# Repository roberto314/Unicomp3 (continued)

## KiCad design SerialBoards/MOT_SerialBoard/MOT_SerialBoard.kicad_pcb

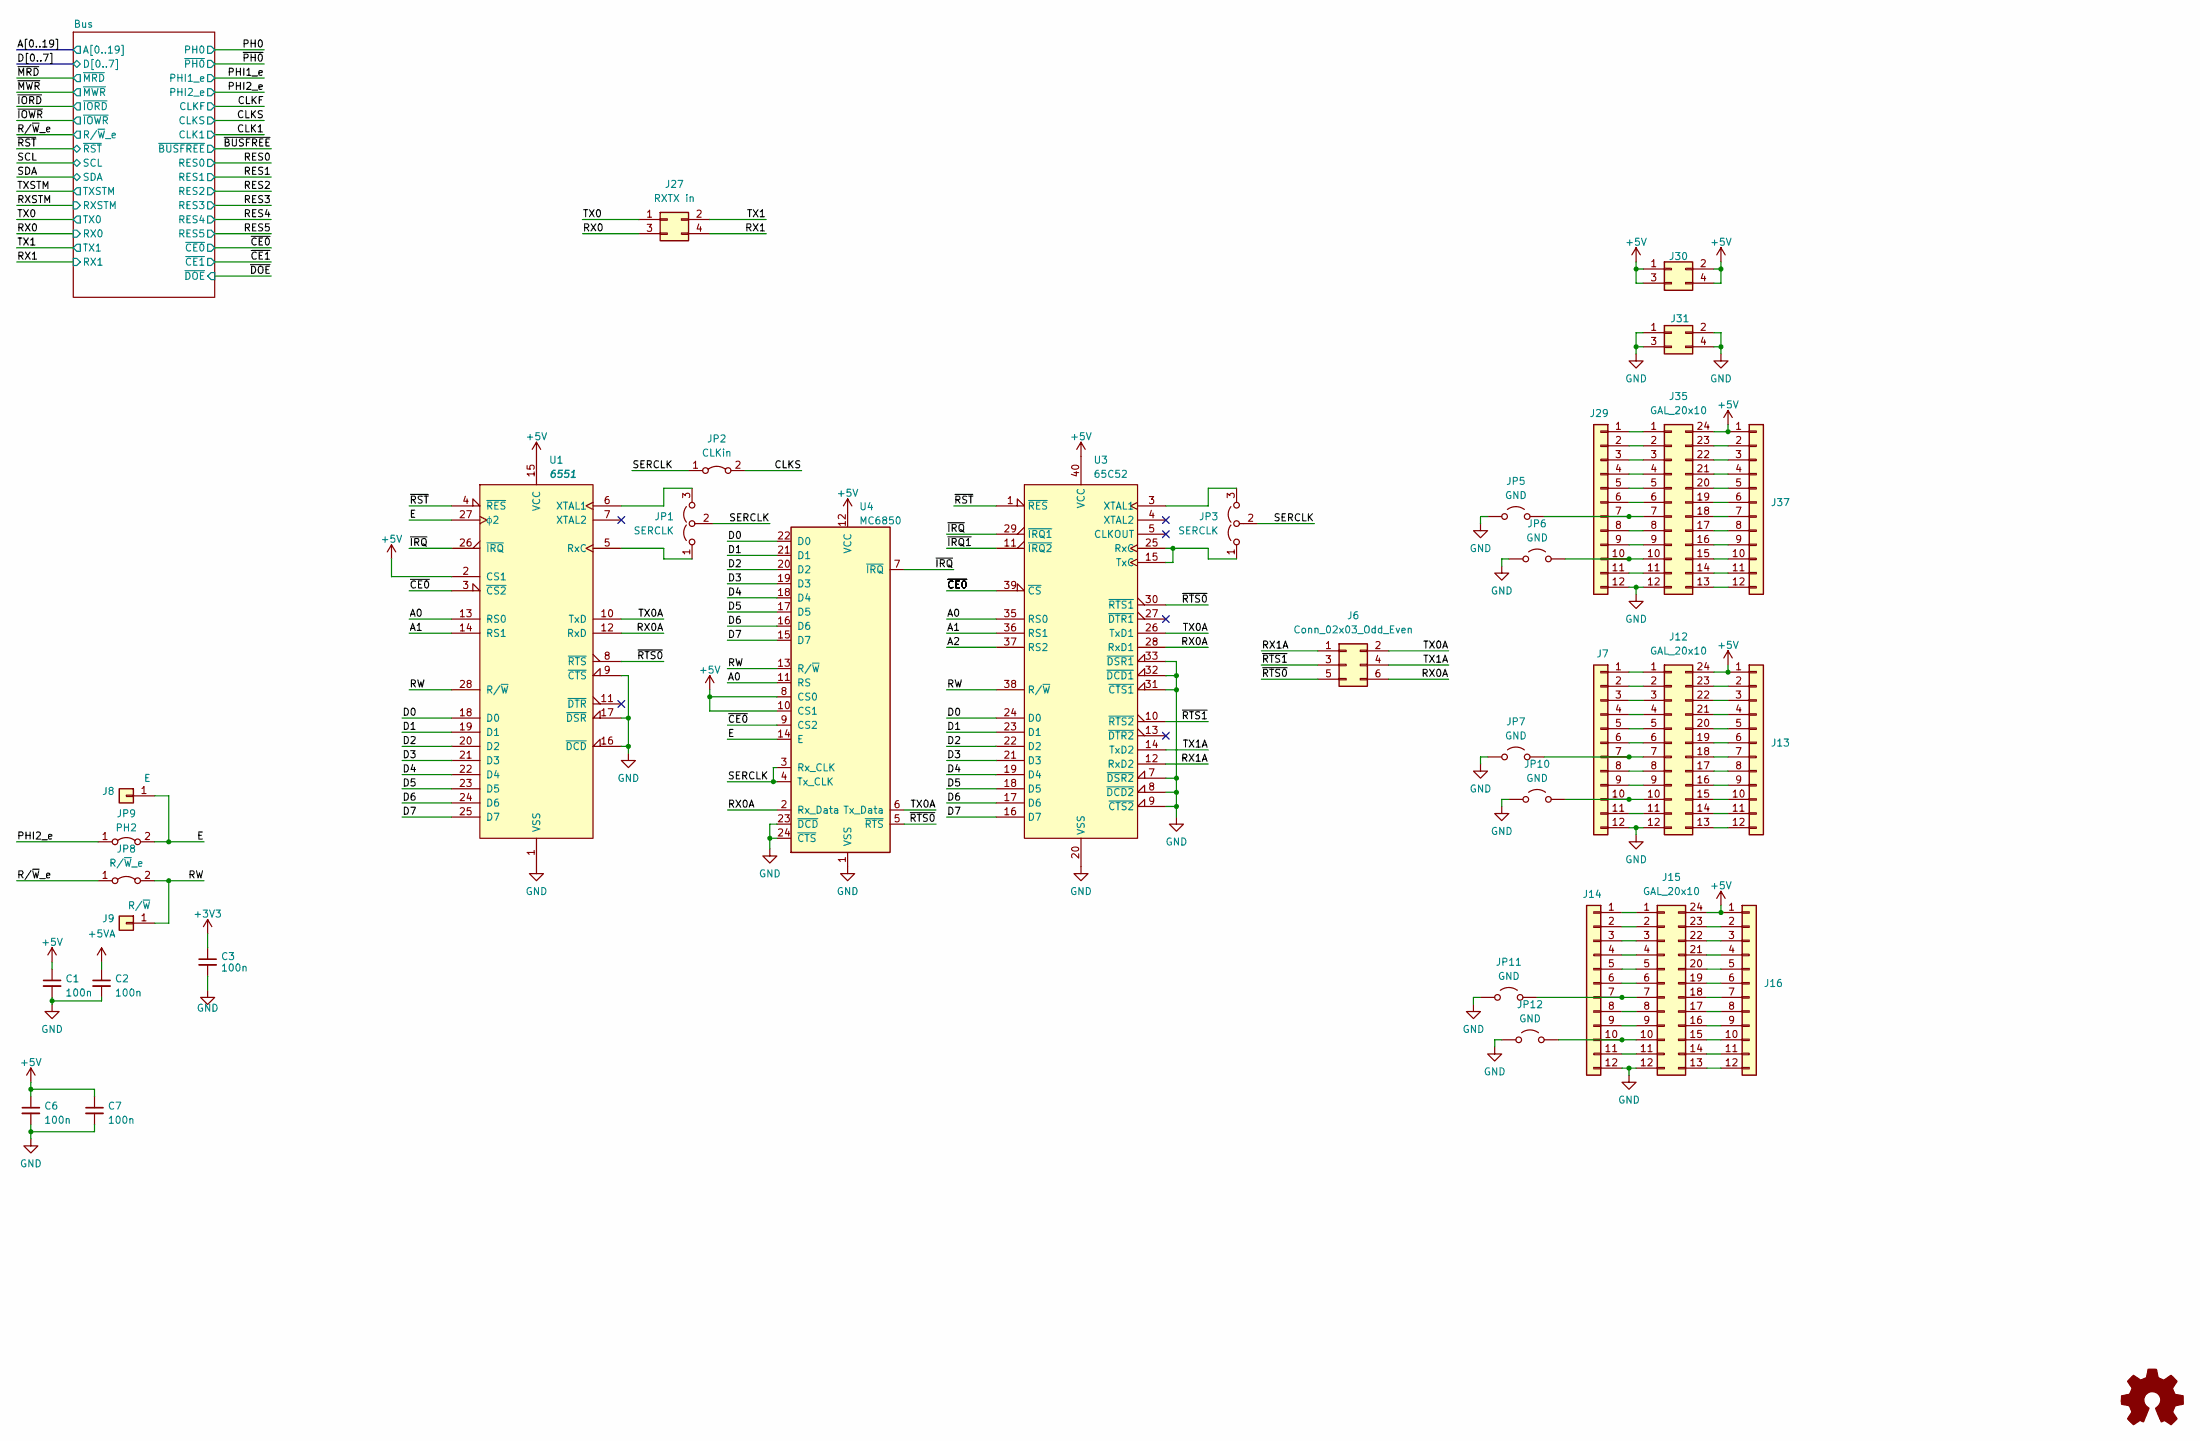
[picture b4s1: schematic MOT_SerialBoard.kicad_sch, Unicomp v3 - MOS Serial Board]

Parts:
C1, C2, C3, C6, C7: 100n; C_1206_3216Metric
J6: Conn_02x03_Odd_Even; PinSocket_2x03_P2.54mm_Vertical
J7, J13, J14, J16, J29, J37: Conn_01x12; PinSocket_1x12_P2.54mm_Vertical
J8: E; PinHeader_1x01_P2.00mm_Vertical
J9: R/~{W}; PinHeader_1x01_P2.00mm_Vertical
J12, J15, J35: GAL_20x10; DIP-24_W7.62mm
J27: RXTX in; PinSocket_2x02_P2.54mm_Vertical
J30, J31: Conn_02x02_Odd_Even; PinSocket_2x02_P2.54mm_Vertical
JP1, JP3: SERCLK; PinHeader_1x03_P2.54mm_Vertical
JP2: CLKin; SolderJumper-2_P1.3mm_Bridged_RoundedPad1.0x1.5mm
JP5, JP6, JP7, JP10, JP11, JP12: GND; SolderJumper-2_P1.3mm_Open_RoundedPad1.0x1.5mm
JP8: R/~{W}_e; SolderJumper-2_P1.3mm_Bridged_RoundedPad1.0x1.5mm
JP9: PH2; SolderJumper-2_P1.3mm_Bridged_RoundedPad1.0x1.5mm
U1: 6551; DIP-28_W15.24mm_LongPads
U3: 65C52; DIP-40_W15.24mm_Socket_LongPads
U4: MC6850; DIP-24_W15.24mm_LongPads

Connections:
+3V3: C3.1; also elsewhere on the board
+5V: C1.1, C6.1, C7.1, J12.24, J13.1, J15.24, J16.1, J30.1, J30.2, J30.3, J30.4, J35.24, J37.1, U1.2 (CS1), U1.15 (VCC), U3.40 (VCC), U4.8 (CS0), U4.10 (CS1), U4.12 (VCC); also elsewhere on the board
+5VA: C2.1; also elsewhere on the board
/A0: U1.13 (RS0), U3.35 (RS0), U4.11 (RS); also elsewhere on the board
/A1: U1.14 (RS1), U3.36 (RS1); also elsewhere on the board
/A2: U3.37 (RS2); also elsewhere on the board
/CLKS: JP2.2 (B); also elsewhere on the board
/D0: U1.18 (D0), U3.24 (D0), U4.22 (D0); also elsewhere on the board
/D1: U1.19 (D1), U3.23 (D1), U4.21 (D1); also elsewhere on the board
/D2: U1.20 (D2), U3.22 (D2), U4.20 (D2); also elsewhere on the board
/D3: U1.21 (D3), U3.21 (D3), U4.19 (D3); also elsewhere on the board
/D4: U1.22 (D4), U3.19 (D4), U4.18 (D4); also elsewhere on the board
/D5: U1.23 (D5), U3.18 (D5), U4.17 (D5); also elsewhere on the board
/D6: U1.24 (D6), U3.17 (D6), U4.16 (D6); also elsewhere on the board
/D7: U1.25 (D7), U3.16 (D7), U4.15 (D7); also elsewhere on the board
/E: J8.1, JP9.2 (B), U1.27 (ϕ2), U4.14 (E)
/PHI2_e: JP9.1 (A); also elsewhere on the board
/RW: J9.1, JP8.2 (B), U1.28 (R/~W), U3.38 (R/~W), U4.13 (R/~W)
/RX0: J27.3; also elsewhere on the board
/RX0A: J6.6, U1.12 (RxD), U3.28 (RxD1), U4.2 (Rx_Data)
/RX1: J27.4; also elsewhere on the board
/RX1A: J6.1, U3.12 (RxD2)
/R/~W_e: JP8.1 (A); also elsewhere on the board
/SERCLK: JP1.2 (C), JP2.1 (A), JP3.2 (C), U4.3 (Rx_CLK), U4.4 (Tx_CLK)
/TX0: J27.1; also elsewhere on the board
/TX0A: J6.2, U1.10 (TxD), U3.26 (TxD1), U4.6 (Tx_Data)
/TX1: J27.2; also elsewhere on the board
/TX1A: J6.4, U3.14 (TxD2)
/~CE0: U1.3 (~CS2), U3.39 (~CS), U4.9 (CS2); also elsewhere on the board
/~IRQ1: U3.11 (~IRQ2)
/~IRQ: U1.26 (~IRQ), U3.29 (~IRQ1), U4.7 (~IRQ)
/~RST: U1.4 (~RES), U3.1 (~RES); also elsewhere on the board
/~RTS0: J6.5, U1.8 (~RTS), U3.30 (~RTS1), U4.5 (~RTS)
/~RTS1: J6.3, U3.10 (~RTS2)
GND: C1.2, C2.2, C3.2, C6.2, C7.2, J7.12, J12.12, J14.12, J15.12, J29.12, J31.1, J31.2, J31.3, J31.4, J35.12, JP5.1 (A), JP6.1 (A), JP7.1 (A), JP10.1 (A), JP11.1 (A), JP12.1 (A), U1.1 (VSS), U1.9 (~CTS), U1.16 (~DCD), U1.17 (~DSR), U3.7 (~DSR2), U3.8 (~DCD2), U3.9 (~CTS2), U3.20 (VSS), U3.31 (~CTS1), U3.32 (~DCD1), U3.33 (~DSR1), U4.1 (VSS), U4.23 (~DCD), U4.24 (~CTS); also elsewhere on the board
unnamed: J7.1, J12.1
unnamed: J7.2, J12.2
unnamed: J7.3, J12.3
unnamed: J7.4, J12.4
unnamed: J7.5, J12.5
unnamed: J7.6, J12.6
unnamed: J7.7, J12.7, JP7.2 (B)
unnamed: J7.8, J12.8
unnamed: J7.9, J12.9
unnamed: J7.10, J12.10, JP10.2 (B)
unnamed: J7.11, J12.11
unnamed: J12.13, J13.12
unnamed: J12.14, J13.11
unnamed: J12.15, J13.10
unnamed: J12.16, J13.9
unnamed: J12.17, J13.8
unnamed: J12.18, J13.7
unnamed: J12.19, J13.6
unnamed: J12.20, J13.5
unnamed: J12.21, J13.4
unnamed: J12.22, J13.3
unnamed: J12.23, J13.2
unnamed: J14.1, J15.1
unnamed: J14.2, J15.2
unnamed: J14.3, J15.3
unnamed: J14.4, J15.4
unnamed: J14.5, J15.5
unnamed: J14.6, J15.6
unnamed: J14.7, J15.7, JP11.2 (B)
unnamed: J14.8, J15.8
unnamed: J14.9, J15.9
unnamed: J14.10, J15.10, JP12.2 (B)
unnamed: J14.11, J15.11
unnamed: J15.13, J16.12
unnamed: J15.14, J16.11
unnamed: J15.15, J16.10
unnamed: J15.16, J16.9
unnamed: J15.17, J16.8
unnamed: J15.18, J16.7
unnamed: J15.19, J16.6
unnamed: J15.20, J16.5
unnamed: J15.21, J16.4
unnamed: J15.22, J16.3
unnamed: J15.23, J16.2
unnamed: J29.1, J35.1
unnamed: J29.2, J35.2
unnamed: J29.3, J35.3
unnamed: J29.4, J35.4
unnamed: J29.5, J35.5
unnamed: J29.6, J35.6
unnamed: J29.7, J35.7, JP5.2 (B)
unnamed: J29.8, J35.8
unnamed: J29.9, J35.9
unnamed: J29.10, J35.10, JP6.2 (B)
unnamed: J29.11, J35.11
unnamed: J35.13, J37.12
unnamed: J35.14, J37.11
unnamed: J35.15, J37.10
unnamed: J35.16, J37.9
unnamed: J35.17, J37.8
unnamed: J35.18, J37.7
unnamed: J35.19, J37.6
unnamed: J35.20, J37.5
unnamed: J35.21, J37.4
unnamed: J35.22, J37.3
unnamed: J35.23, J37.2
unnamed: JP1.1 (A), U1.5 (RxC)
unnamed: JP1.3 (B), U1.6 (XTAL1)
unnamed: JP3.1 (A), U3.15 (TxC), U3.25 (RxC)
unnamed: JP3.3 (B), U3.3 (XTAL1)

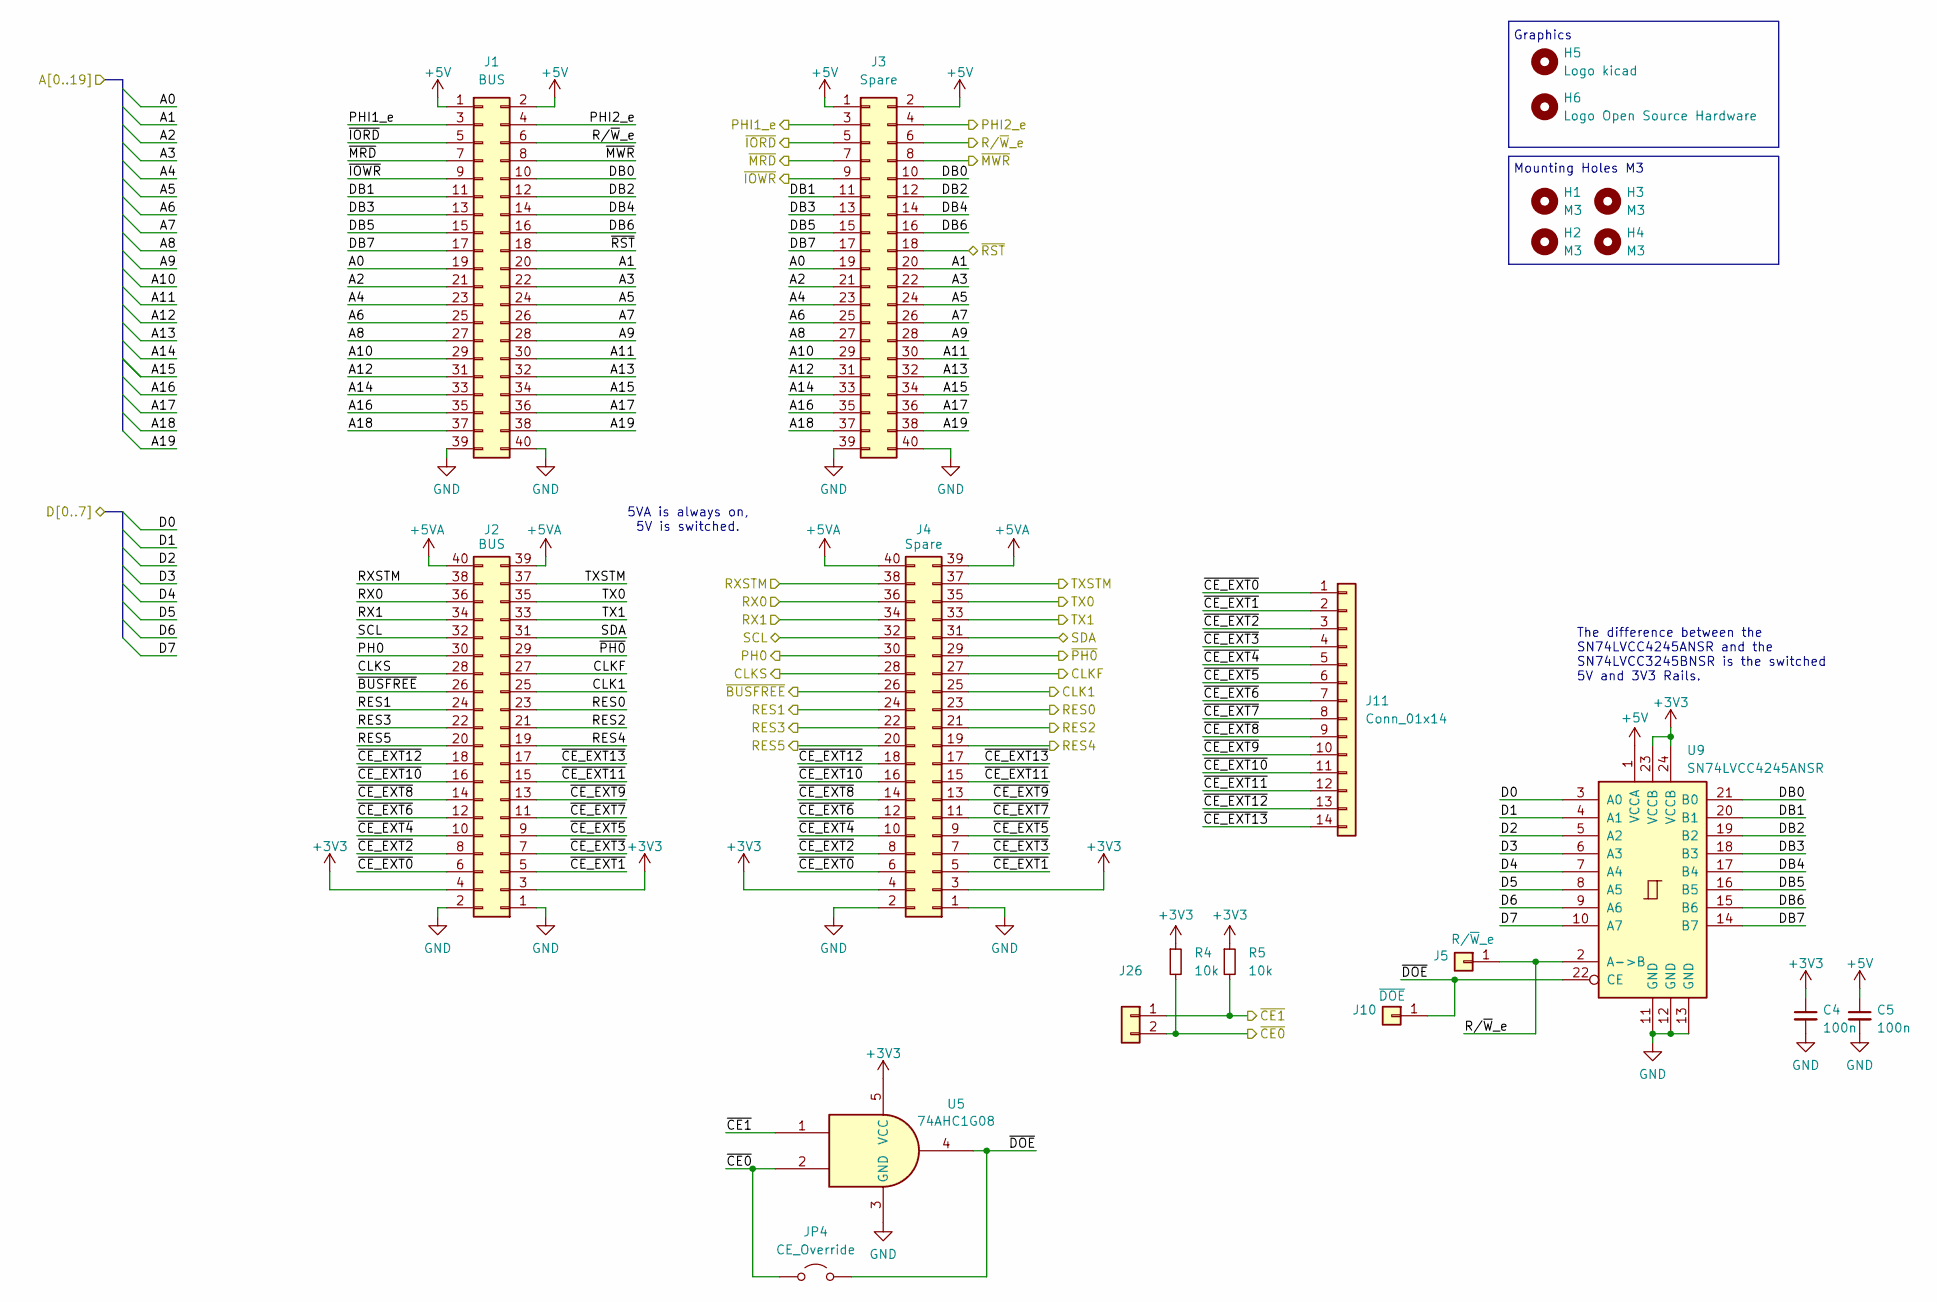
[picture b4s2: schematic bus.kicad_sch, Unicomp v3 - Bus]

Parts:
C4, C5: 100n; C_1206_3216Metric
H1, H2, H3, H4: M3; MountingHole_3.2mm_M3
H5: Logo kicad; KiCad-Logo2_6mm_SilkScreen
H6: Logo Open Source Hardware; OSHW-Logo2_7.3x6mm_SilkScreen
J1, J2: BUS; PinSocket_2x20_P2.54mm_Vertical
J3, J4: Spare; PinSocket_2x20_P2.54mm_Vertical
J5: R/~{W}_e; PinHeader_1x01_P2.00mm_Vertical
J10: ~{DOE}; PinHeader_1x01_P2.00mm_Vertical
J11: Conn_01x14; PinSocket_1x14_P2.54mm_Vertical
J26: Conn_01x02; PinSocket_1x02_P2.54mm_Vertical
JP4: CE_Override; SolderJumper-2_P1.3mm_Open_RoundedPad1.0x1.5mm
R4, R5: 10k; R_1206_3216Metric_Pad1.30x1.75mm_HandSolder
U5: 74AHC1G08; SOT-23-5_HandSoldering
U9: SN74LVCC4245ANSR; SO-24_5.3x15mm_P1.27mm

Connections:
+3V3: C4.1, J2.3, J2.4, J4.3, J4.4, R4.1, R5.1, U5.5 (VCC), U9.23 (VCCB), U9.24 (VCCB); also elsewhere on the board
+5V: C5.1, J1.1, J1.2, J3.1, J3.2, U9.1 (VCCA); also elsewhere on the board
+5VA: J2.39, J2.40, J4.39, J4.40; also elsewhere on the board
/A0: J1.19, J3.19; also elsewhere on the board
/A1: J1.20, J3.20; also elsewhere on the board
/A2: J1.21, J3.21; also elsewhere on the board
/A3: J1.22, J3.22
/A4: J1.23, J3.23
/A5: J1.24, J3.24
/A6: J1.25, J3.25
/A7: J1.26, J3.26
/A8: J1.27, J3.27
/A9: J1.28, J3.28
/A10: J1.29, J3.29
/A11: J1.30, J3.30
/A12: J1.31, J3.31
/A13: J1.32, J3.32
/A14: J1.33, J3.33
/A15: J1.34, J3.34
/A16: J1.35, J3.35
/A17: J1.36, J3.36
/A18: J1.37, J3.37
/A19: J1.38, J3.38
/Bus/DB0: J1.10, J3.10, U9.21 (B0)
/Bus/DB1: J1.11, J3.11, U9.20 (B1)
/Bus/DB2: J1.12, J3.12, U9.19 (B2)
/Bus/DB3: J1.13, J3.13, U9.18 (B3)
/Bus/DB4: J1.14, J3.14, U9.17 (B4)
/Bus/DB5: J1.15, J3.15, U9.16 (B5)
/Bus/DB6: J1.16, J3.16, U9.15 (B6)
/Bus/DB7: J1.17, J3.17, U9.14 (B7)
/Bus/~CE_EXT0: J2.6, J4.6, J11.1
/Bus/~CE_EXT1: J2.5, J4.5, J11.2
/Bus/~CE_EXT2: J2.8, J4.8, J11.3
/Bus/~CE_EXT3: J2.7, J4.7, J11.4
/Bus/~CE_EXT4: J2.10, J4.10, J11.5
/Bus/~CE_EXT5: J2.9, J4.9, J11.6
/Bus/~CE_EXT6: J2.12, J4.12, J11.7
/Bus/~CE_EXT7: J2.11, J4.11, J11.8
/Bus/~CE_EXT8: J2.14, J4.14, J11.9
/Bus/~CE_EXT9: J2.13, J4.13, J11.10
/Bus/~CE_EXT10: J2.16, J4.16, J11.11
/Bus/~CE_EXT11: J2.15, J4.15, J11.12
/Bus/~CE_EXT12: J2.18, J4.18, J11.13
/Bus/~CE_EXT13: J2.17, J4.17, J11.14
/Bus/~DOE: J10.1, JP4.2 (B), U5.4, U9.22 (CE)
/CLK1: J2.25, J4.25
/CLKF: J2.27, J4.27
/CLKS: J2.28, J4.28; also elsewhere on the board
/D0: U9.3 (A0); also elsewhere on the board
/D1: U9.4 (A1); also elsewhere on the board
/D2: U9.5 (A2); also elsewhere on the board
/D3: U9.6 (A3); also elsewhere on the board
/D4: U9.7 (A4); also elsewhere on the board
/D5: U9.8 (A5); also elsewhere on the board
/D6: U9.9 (A6); also elsewhere on the board
/D7: U9.10 (A7); also elsewhere on the board
/PH0: J2.30, J4.30
/PHI1_e: J1.3, J3.3
/PHI2_e: J1.4, J3.4; also elsewhere on the board
/RES0: J2.23, J4.23
/RES1: J2.24, J4.24
/RES2: J2.21, J4.21
/RES3: J2.22, J4.22
/RES4: J2.19, J4.19
/RES5: J2.20, J4.20
/RX0: J2.36, J4.36; also elsewhere on the board
/RX1: J2.34, J4.34; also elsewhere on the board
/RXSTM: J2.38, J4.38
/R/~W_e: J1.6, J3.6, J5.1, U9.2 (A->B); also elsewhere on the board
/SCL: J2.32, J4.32
/SDA: J2.31, J4.31
/TX0: J2.35, J4.35; also elsewhere on the board
/TX1: J2.33, J4.33; also elsewhere on the board
/TXSTM: J2.37, J4.37
/~BUSFREE: J2.26, J4.26
/~CE0: J26.2, JP4.1 (A), R4.2, U5.2; also elsewhere on the board
/~CE1: J26.1, R5.2, U5.1
/~IORD: J1.5, J3.5
/~IOWR: J1.9, J3.9
/~MRD: J1.7, J3.7
/~MWR: J1.8, J3.8
/~PH0: J2.29, J4.29
/~RST: J1.18, J3.18; also elsewhere on the board
GND: C4.2, C5.2, J1.39, J1.40, J2.1, J2.2, J3.39, J3.40, J4.1, J4.2, U5.3 (GND), U9.11 (GND), U9.12 (GND), U9.13 (GND); also elsewhere on the board

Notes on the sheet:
Graphics
5VA is always on, 5V is switched.
Mounting Holes M3
The difference between the SN74LVCC4245ANSR and the SN74LVCC3245BNSR is the switched 5V and 3V3 Rails.

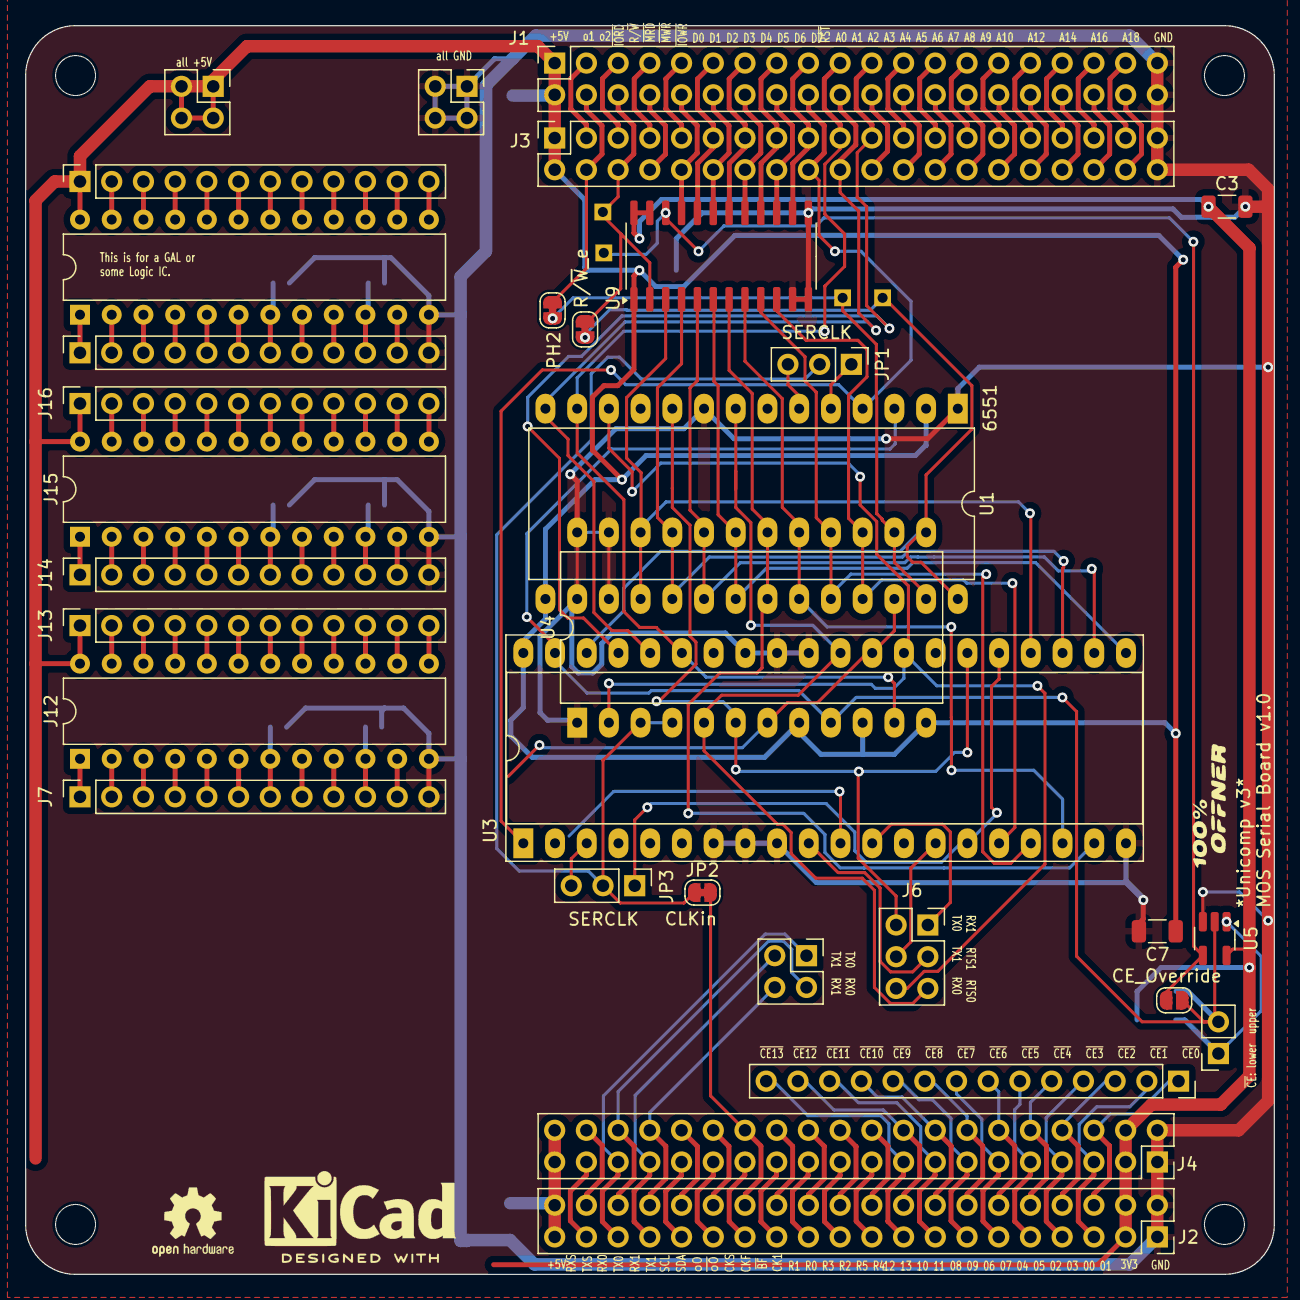
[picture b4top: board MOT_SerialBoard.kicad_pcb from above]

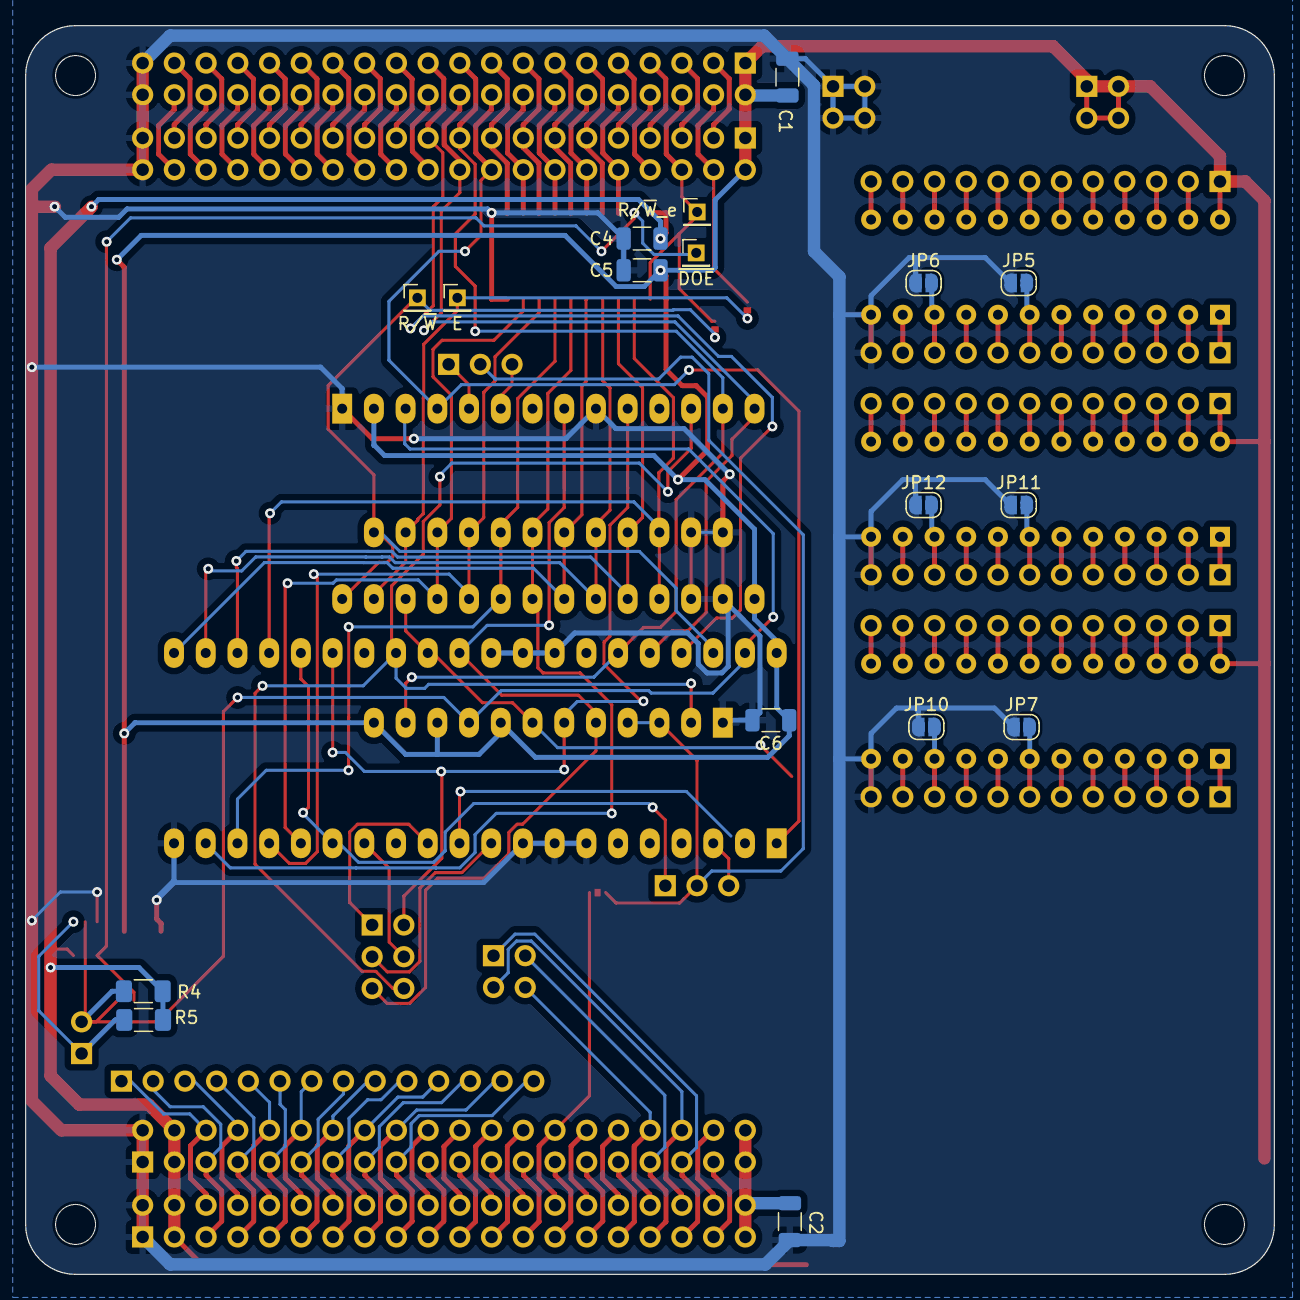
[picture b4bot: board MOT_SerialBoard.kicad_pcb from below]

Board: 2 copper layers, 100.0 x 100.0 mm, 55 parts (17 on the bottom side), 165 nets.

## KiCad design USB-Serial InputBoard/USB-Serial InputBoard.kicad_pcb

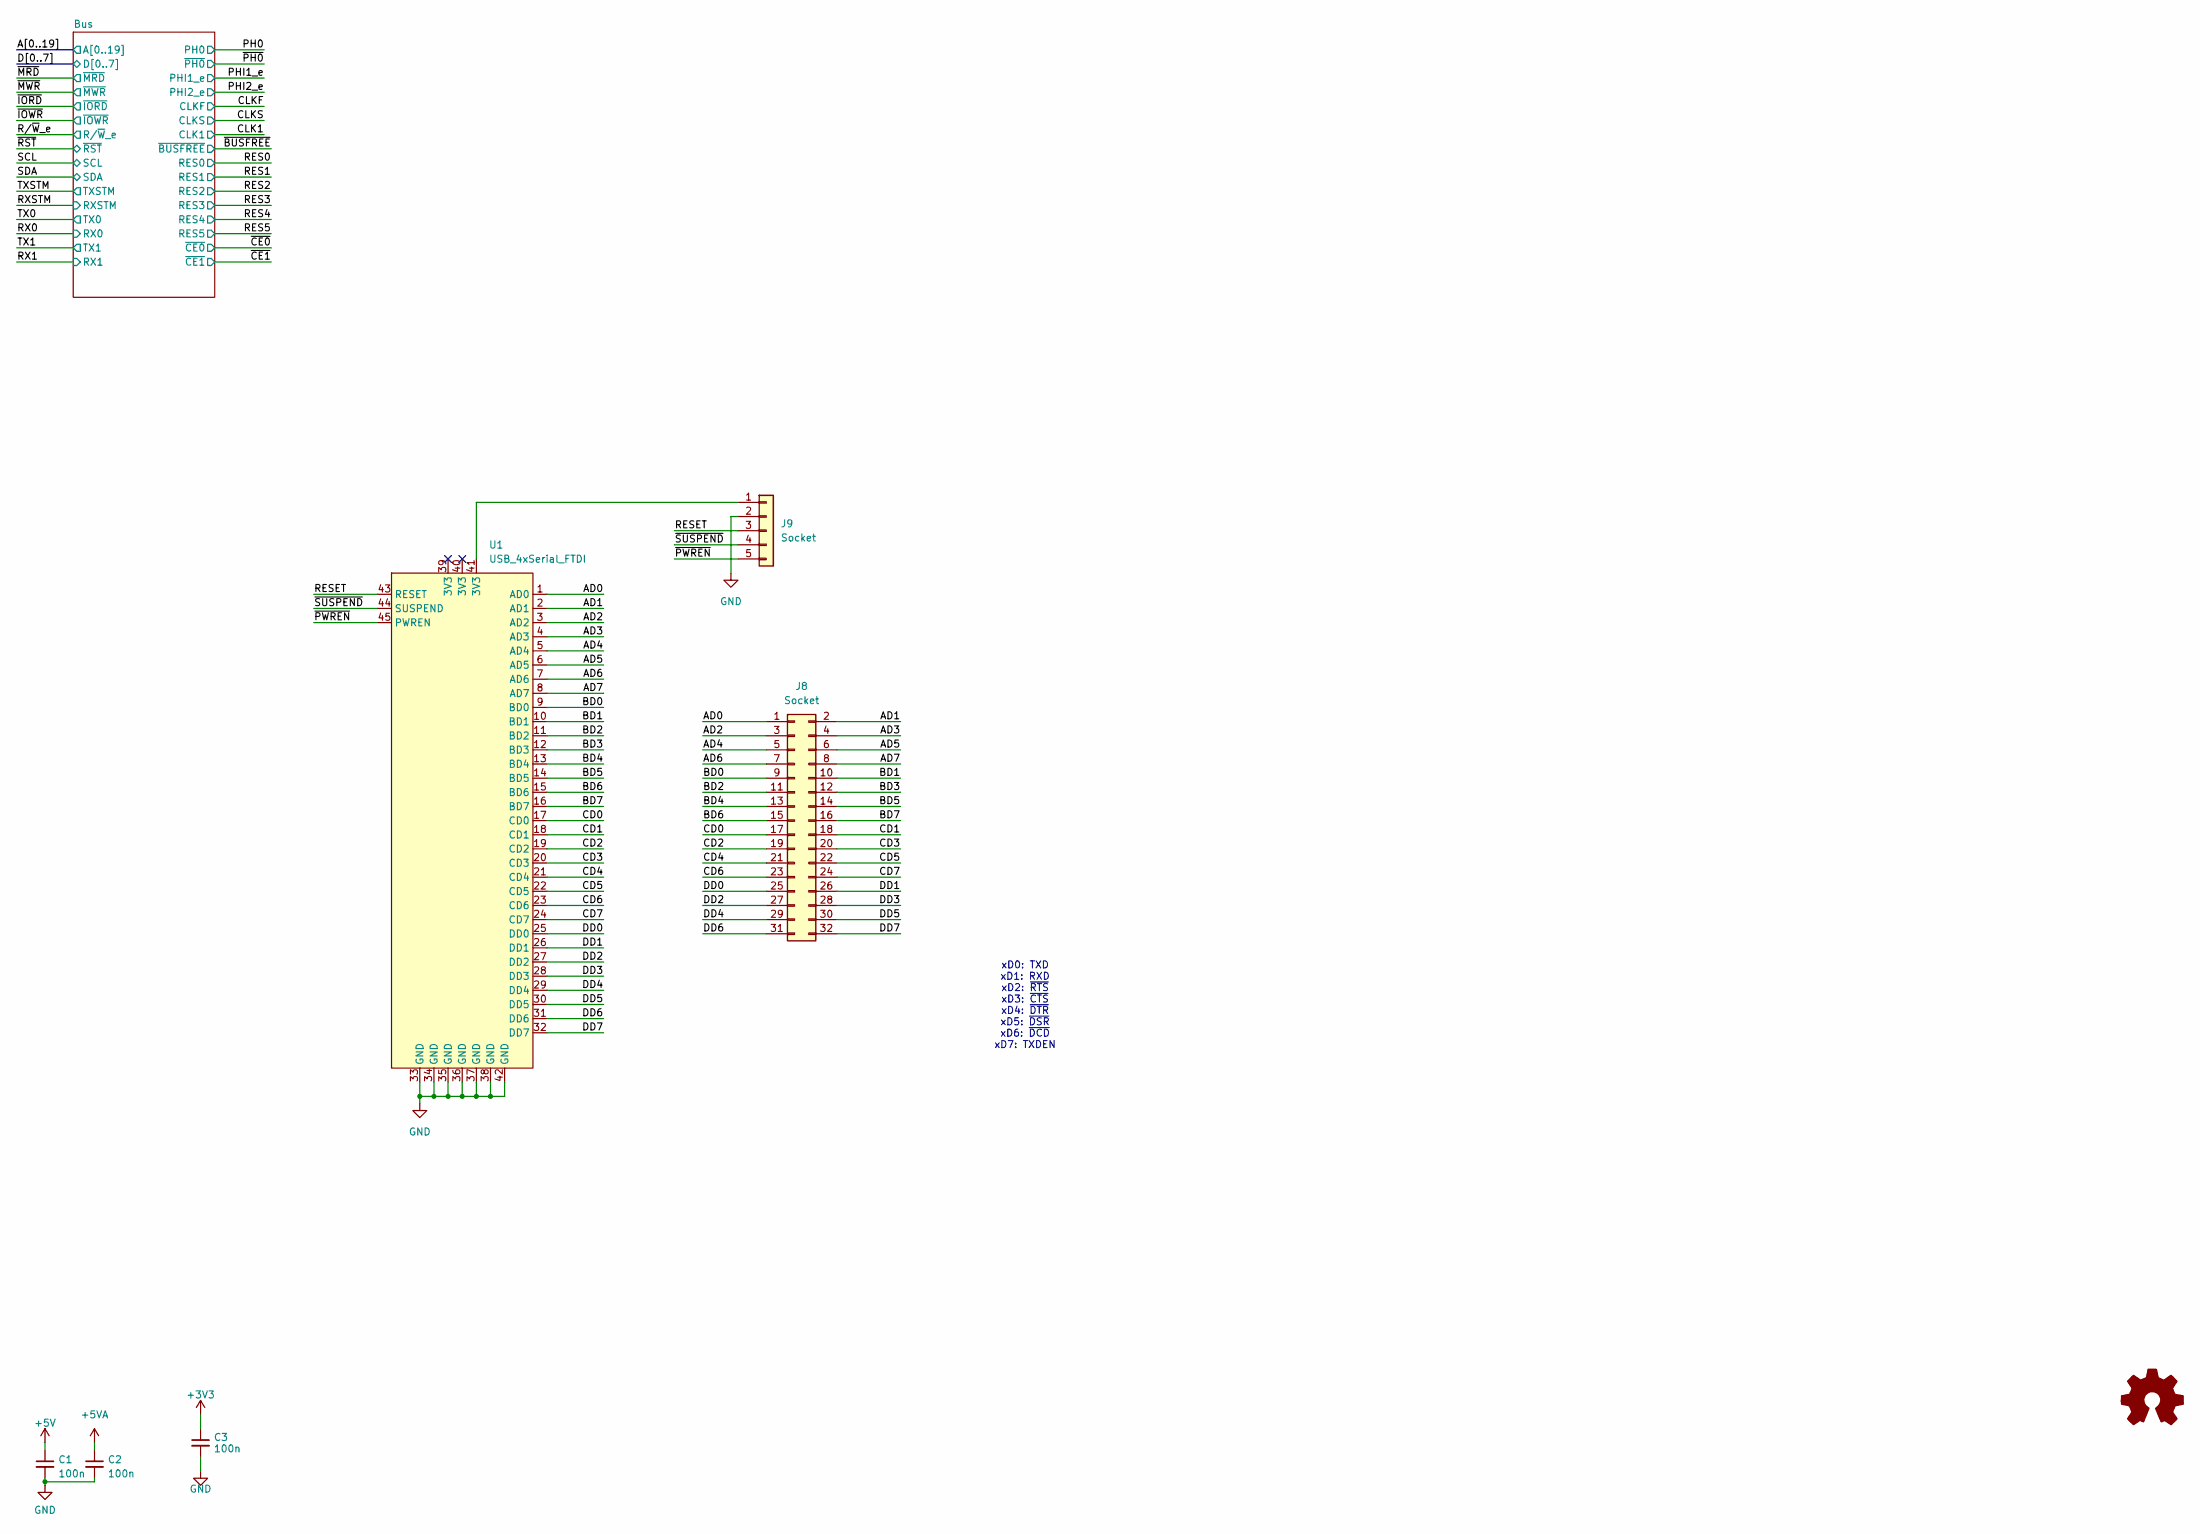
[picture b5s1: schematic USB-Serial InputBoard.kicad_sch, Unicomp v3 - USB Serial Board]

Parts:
C1, C2, C3: 100n; C_1206_3216Metric
J8: Socket; PinSocket_2x16_P2.54mm_Vertical
J9: Socket; PinSocket_1x05_P2.54mm_Vertical
U1: USB_4xSerial_FTDI

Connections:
+3V3: C3.1; also elsewhere on the board
+5V: C1.1; also elsewhere on the board
+5VA: C2.1; also elsewhere on the board
/AD0: J8.1, U1.1 (AD0)
/AD1: J8.2, U1.2 (AD1)
/AD2: J8.3, U1.3 (AD2)
/AD3: J8.4, U1.4 (AD3)
/AD4: J8.5, U1.5 (AD4)
/AD5: J8.6, U1.6 (AD5)
/AD6: J8.7, U1.7 (AD6)
/AD7: J8.8, U1.8 (AD7)
/BD0: J8.9, U1.9 (BD0)
/BD1: J8.10, U1.10 (BD1)
/BD2: J8.11, U1.11 (BD2)
/BD3: J8.12, U1.12 (BD3)
/BD4: J8.13, U1.13 (BD4)
/BD5: J8.14, U1.14 (BD5)
/BD6: J8.15, U1.15 (BD6)
/BD7: J8.16, U1.16 (BD7)
/CD0: J8.17, U1.17 (CD0)
/CD1: J8.18, U1.18 (CD1)
/CD2: J8.19, U1.19 (CD2)
/CD3: J8.20, U1.20 (CD3)
/CD4: J8.21, U1.21 (CD4)
/CD5: J8.22, U1.22 (CD5)
/CD6: J8.23, U1.23 (CD6)
/CD7: J8.24, U1.24 (CD7)
/DD0: J8.25, U1.25 (DD0)
/DD1: J8.26, U1.26 (DD1)
/DD2: J8.27, U1.27 (DD2)
/DD3: J8.28, U1.28 (DD3)
/DD4: J8.29, U1.29 (DD4)
/DD5: J8.30, U1.30 (DD5)
/DD6: J8.31, U1.31 (DD6)
/DD7: J8.32, U1.32 (DD7)
/RESET: J9.3, U1.43 (RESET)
/~PWREN: J9.5, U1.45 (PWREN)
/~SUSPEND: J9.4, U1.44 (SUSPEND)
GND: C1.2, C2.2, C3.2, J9.2, U1.33 (GND), U1.34 (GND), U1.35 (GND), U1.36 (GND), U1.37 (GND), U1.38 (GND), U1.42 (GND); also elsewhere on the board
unnamed: J9.1, U1.41 (3V3)

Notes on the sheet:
xD0: TXD xD1: RXD xD2: ~{RTS} xD3: ~{CTS} xD4: ~{DTR} xD5: ~{DSR} xD6: ~{DCD} xD7: TXDEN

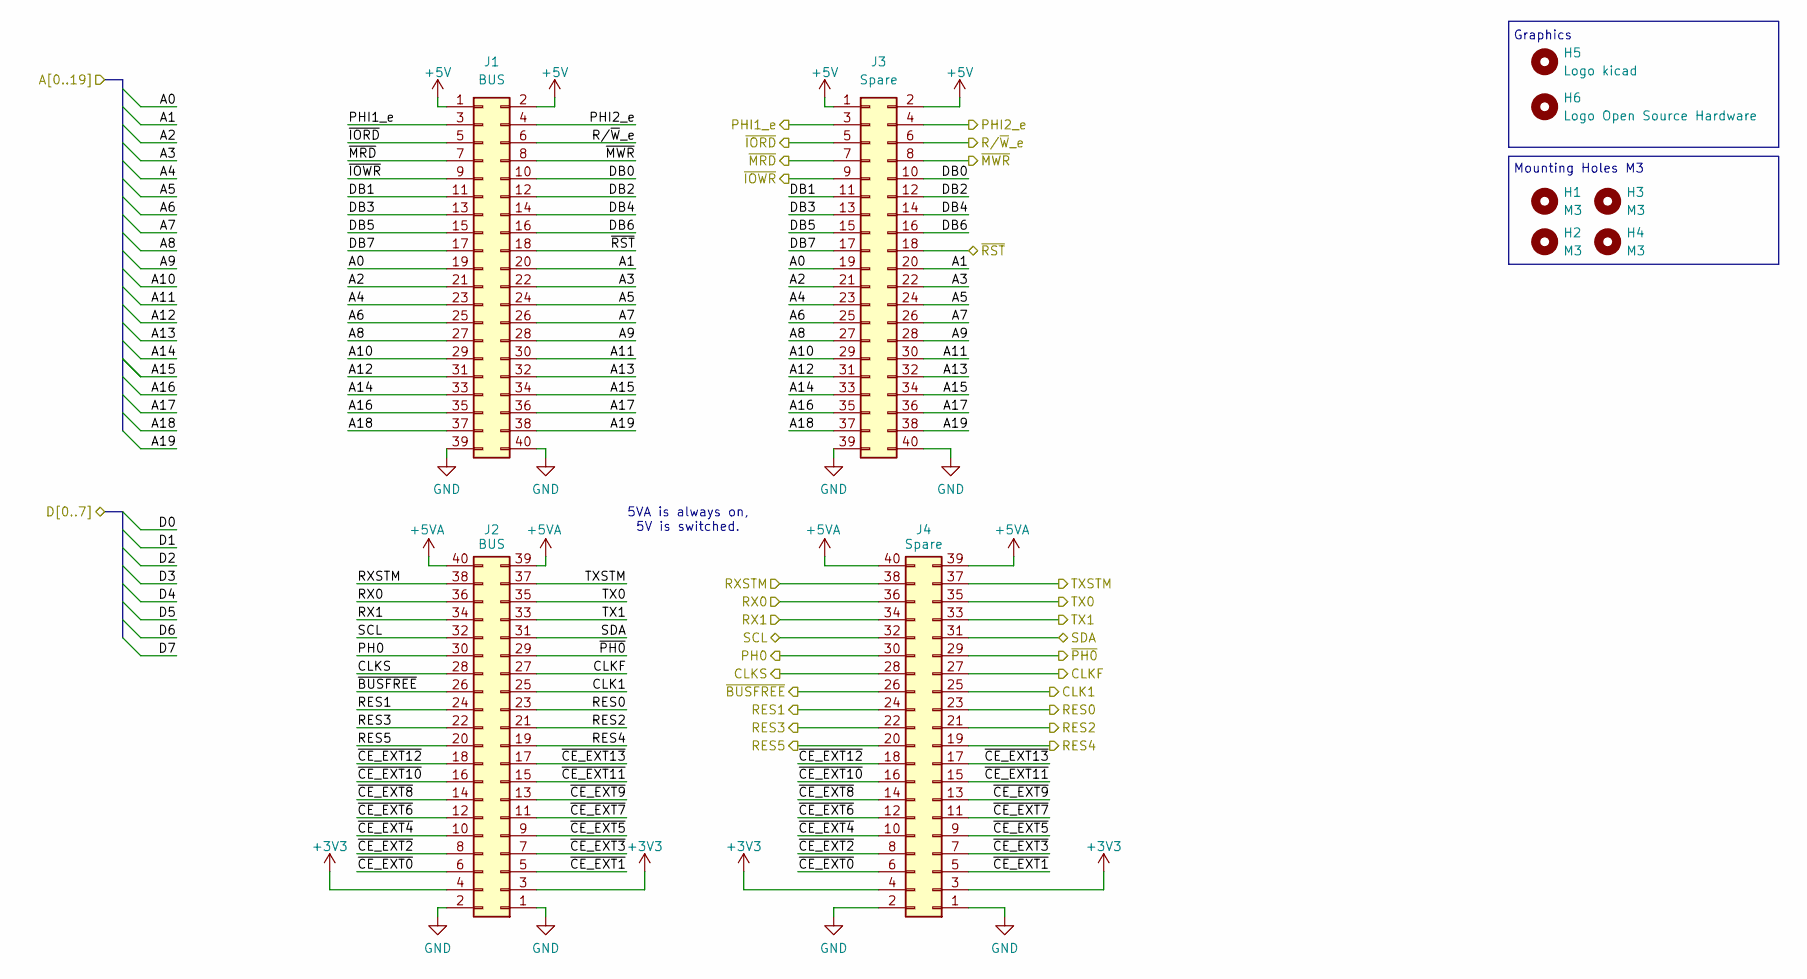
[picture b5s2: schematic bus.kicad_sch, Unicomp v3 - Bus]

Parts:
H1, H2, H3, H4: M3; MountingHole_3.2mm_M3
H5: Logo kicad; KiCad-Logo2_6mm_SilkScreen
H6: Logo Open Source Hardware; OSHW-Logo2_7.3x6mm_SilkScreen
J1, J2: BUS; PinSocket_2x20_P2.54mm_Vertical
J3, J4: Spare; PinSocket_2x20_P2.54mm_Vertical

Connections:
+3V3: J2.3, J2.4, J4.3, J4.4; also elsewhere on the board
+5V: J1.1, J1.2, J3.1, J3.2; also elsewhere on the board
+5VA: J2.39, J2.40, J4.39, J4.40; also elsewhere on the board
/A0: J1.19, J3.19
/A1: J1.20, J3.20
/A2: J1.21, J3.21
/A3: J1.22, J3.22
/A4: J1.23, J3.23
/A5: J1.24, J3.24
/A6: J1.25, J3.25
/A7: J1.26, J3.26
/A8: J1.27, J3.27
/A9: J1.28, J3.28
/A10: J1.29, J3.29
/A11: J1.30, J3.30
/A12: J1.31, J3.31
/A13: J1.32, J3.32
/A14: J1.33, J3.33
/A15: J1.34, J3.34
/A16: J1.35, J3.35
/A17: J1.36, J3.36
/A18: J1.37, J3.37
/A19: J1.38, J3.38
/Bus/DB0: J1.10, J3.10
/Bus/DB1: J1.11, J3.11
/Bus/DB2: J1.12, J3.12
/Bus/DB3: J1.13, J3.13
/Bus/DB4: J1.14, J3.14
/Bus/DB5: J1.15, J3.15
/Bus/DB6: J1.16, J3.16
/Bus/DB7: J1.17, J3.17
/Bus/~CE_EXT0: J2.6, J4.6
/Bus/~CE_EXT1: J2.5, J4.5
/Bus/~CE_EXT2: J2.8, J4.8
/Bus/~CE_EXT3: J2.7, J4.7
/Bus/~CE_EXT4: J2.10, J4.10
/Bus/~CE_EXT5: J2.9, J4.9
/Bus/~CE_EXT6: J2.12, J4.12
/Bus/~CE_EXT7: J2.11, J4.11
/Bus/~CE_EXT8: J2.14, J4.14
/Bus/~CE_EXT9: J2.13, J4.13
/Bus/~CE_EXT10: J2.16, J4.16
/Bus/~CE_EXT11: J2.15, J4.15
/Bus/~CE_EXT12: J2.18, J4.18
/Bus/~CE_EXT13: J2.17, J4.17
/CLK1: J2.25, J4.25
/CLKF: J2.27, J4.27
/CLKS: J2.28, J4.28
/PH0: J2.30, J4.30
/PHI1_e: J1.3, J3.3
/PHI2_e: J1.4, J3.4
/RES0: J2.23, J4.23
/RES1: J2.24, J4.24
/RES2: J2.21, J4.21
/RES3: J2.22, J4.22
/RES4: J2.19, J4.19
/RES5: J2.20, J4.20
/RX0: J2.36, J4.36
/RX1: J2.34, J4.34
/RXSTM: J2.38, J4.38
/R/~W_e: J1.6, J3.6
/SCL: J2.32, J4.32
/SDA: J2.31, J4.31
/TX0: J2.35, J4.35
/TX1: J2.33, J4.33
/TXSTM: J2.37, J4.37
/~BUSFREE: J2.26, J4.26
/~IORD: J1.5, J3.5
/~IOWR: J1.9, J3.9
/~MRD: J1.7, J3.7
/~MWR: J1.8, J3.8
/~PH0: J2.29, J4.29
/~RST: J1.18, J3.18
GND: J1.39, J1.40, J2.1, J2.2, J3.39, J3.40, J4.1, J4.2; also elsewhere on the board

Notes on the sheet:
Graphics
5VA is always on, 5V is switched.
Mounting Holes M3
